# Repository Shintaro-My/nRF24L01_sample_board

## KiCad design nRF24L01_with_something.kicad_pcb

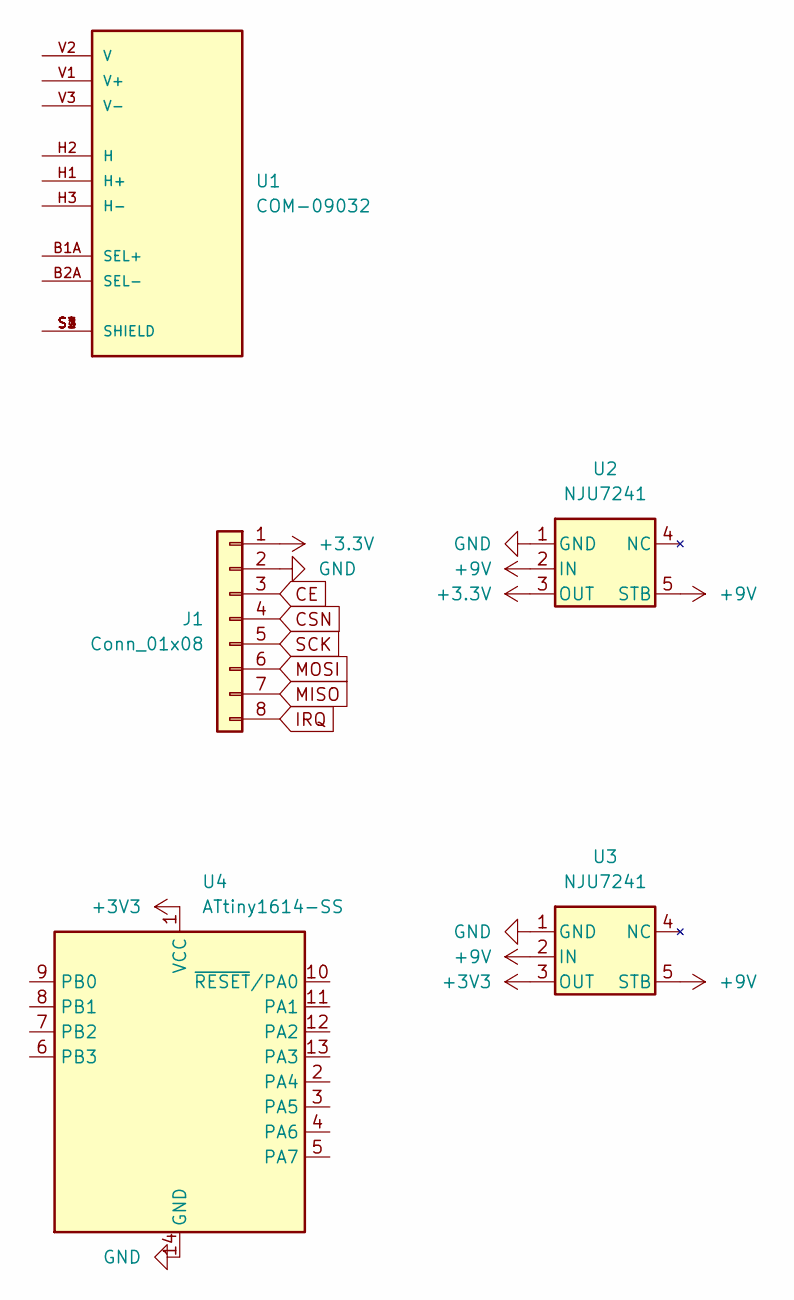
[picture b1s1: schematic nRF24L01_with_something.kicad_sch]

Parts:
J1: Conn_01x08; PinHeader_1x08_P1.27mm_Vertical
U1: COM-09032; XDCR_COM-09032; PARTREV N/A
U2, U3: NJU7241; SOT-23-5
U4: ATtiny1614-SS; SOIC-14_3.9x8.7mm_P1.27mm

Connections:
+3.3V: J1.1, U2.3 (OUT)
+3V3: U3.3 (OUT), U4.1 (VCC)
+9V: U2.2 (IN), U2.5 (STB), U3.2 (IN), U3.5 (STB)
CE: J1.3
CSN: J1.4
GND: J1.2, U2.1 (GND), U3.1 (GND), U4.14 (GND)
IRQ: J1.8
MISO: J1.7
MOSI: J1.6
unnamed: U1.S1 (SHIELD), U1.S2 (SHIELD), U1.S3 (SHIELD), U1.S4 (SHIELD)
SCK: J1.5

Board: 2 copper layers, 5 parts (0 on the bottom side), 5 nets, no tracks yet.
